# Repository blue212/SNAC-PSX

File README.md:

# SNAC
PSX Accessory converter for MiSTer, by blue212

Serial Native Accessory Converter

SNAC adapter for PSX. This board and psx use 3v3 logic. This is a standalone board, so it's not to used with the SNAC level shifter board. You can use a short male to female usb3.0 extension cable between it and misters USER port.

It has two ports for controllers and a composite port for guncon, also has a header for test points. If a guncon is connected and a justifier isn't the needed signal for Guncon will be output through the composite port.

This version has a solder jumper to connect 5v to the 7.6v pin for rumble. You could not solder the jumper and add external power, but be advised that bad things will happen if you mix up polarity.

-TODO 

-Updates

Added Memory Card add-on board. It uses a 0.8mm thick pcb.

Added files for 3D print cases. Designed by [DiniertoDesigns](https://www.thingiverse.com/thing:5530398)

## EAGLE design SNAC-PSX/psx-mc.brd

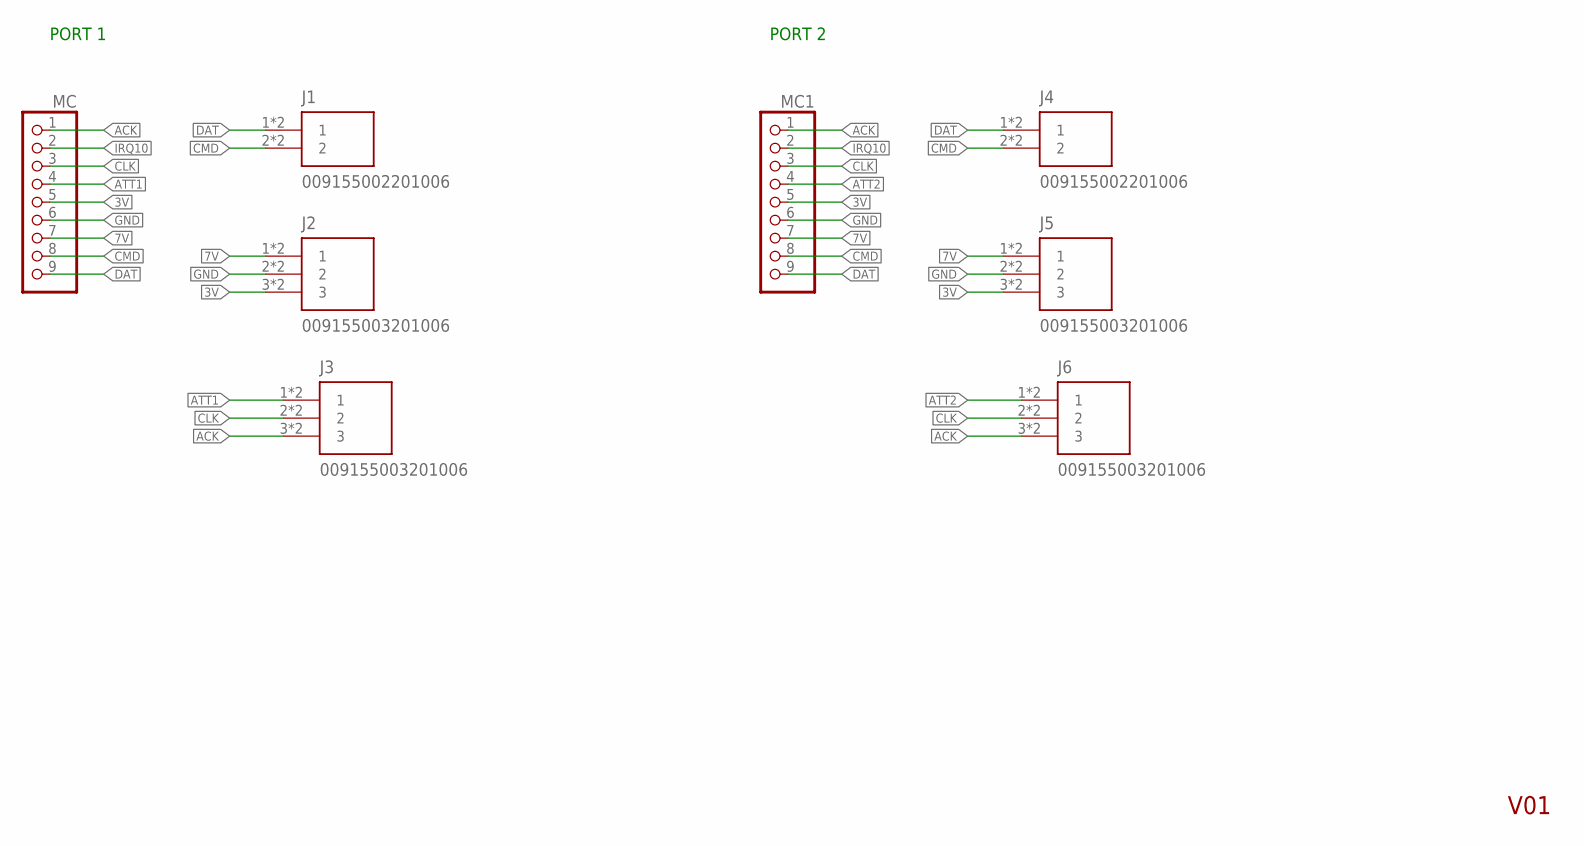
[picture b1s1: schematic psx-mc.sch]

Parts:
J1, J4: 009155002201006; AVX_009155002201006
J2, J3, J5, J6: 009155003201006; AVX_009155003201006
MC, MC1: PINHD-1X09_2.54-S; 1X09-S

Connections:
3V: J2.3, J2.3_1 (3), J5.3, J5.3_1 (3), MC.5, MC1.5
7V: J2.1, J2.1_1 (1), J5.1, J5.1_1 (1), MC.7, MC1.7
ACK: J3.3, J3.3_1 (3), J6.3, J6.3_1 (3), MC.1, MC1.1
ATT1: J3.1, J3.1_1 (1), MC.4
ATT2: J6.1, J6.1_1 (1), MC1.4
CLK: J3.2, J3.2_1 (2), J6.2, J6.2_1 (2), MC.3, MC1.3
CMD: J1.2, J1.2_1 (2), J4.2, J4.2_1 (2), MC.8, MC1.8
DAT: J1.1, J1.1_1 (1), J4.1, J4.1_1 (1), MC.9, MC1.9
GND: J2.2, J2.2_1 (2), J5.2, J5.2_1 (2), MC.6, MC1.6
IRQ10: MC.2, MC1.2

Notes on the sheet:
V01
PORT 1
PORT 2

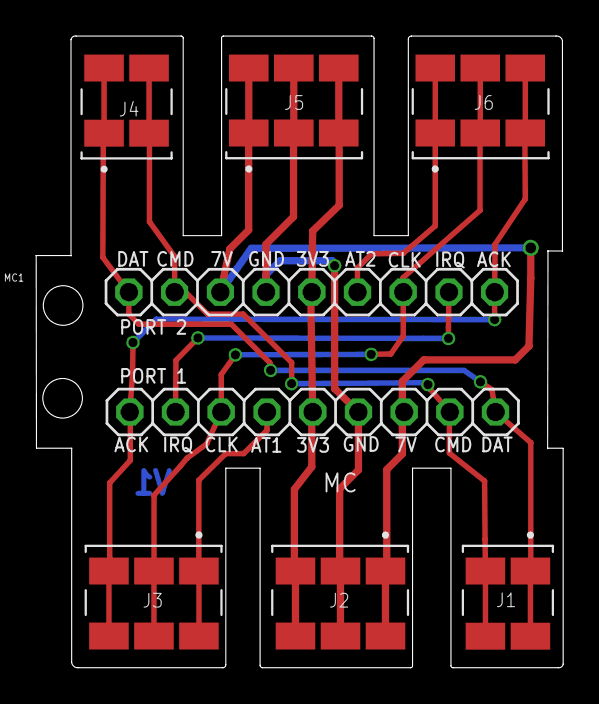
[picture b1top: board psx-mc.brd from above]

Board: 2 copper layers, 29.3 x 35.1 mm, 8 parts (0 on the bottom side), 10 nets.

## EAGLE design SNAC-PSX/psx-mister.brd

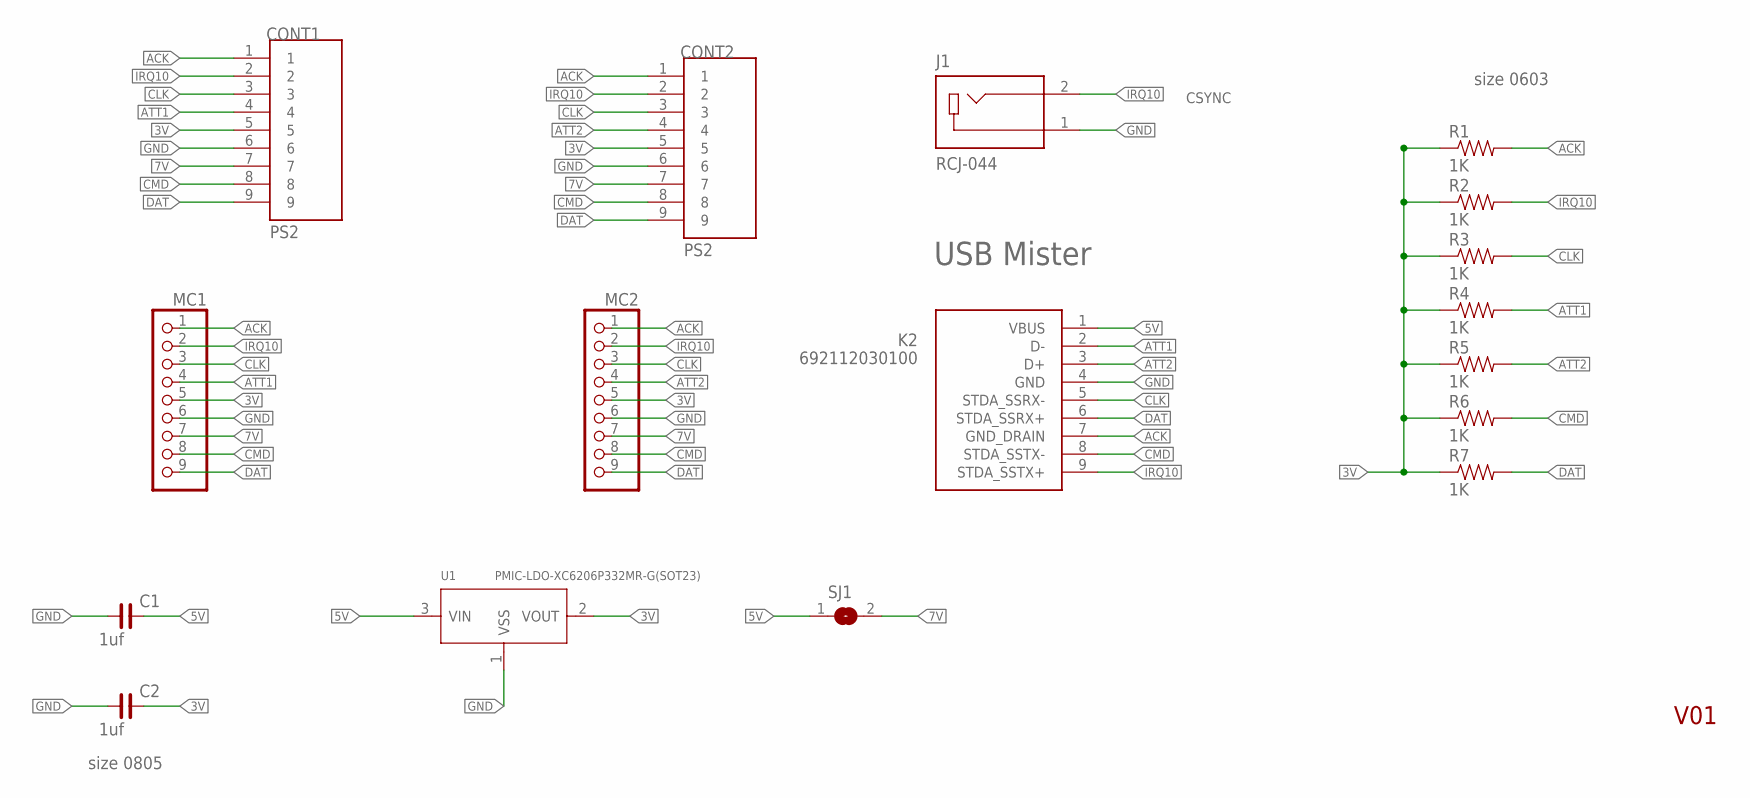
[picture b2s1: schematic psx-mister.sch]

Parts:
C1, C2: 1uf; C0805
CONT1, CONT2: PS2; TE_PS2
J1: RCJ-044; CUI_RCJ-044
K2: 692112030100
MC1, MC2: PINHD-1X09_2.54-S; 1X09-S
R1, R2, R3, R4, R5, R6, R7: 1K; 0603-RES
SJ1: SJ
U1: PMIC-LDO-XC6206P332MR-G(SOT23); SOT-23

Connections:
3V: C2.2, CONT1.5, CONT2.5, MC1.5, MC2.5, R1.1, R2.1, R3.1, R4.1, R5.1, R6.1, R7.1, U1.2 (VOUT)
5V: C1.2, K2.1 (VBUS), SJ1.1, U1.3 (VIN)
7V: CONT1.7, CONT2.7, MC1.7, MC2.7, SJ1.2
ACK: CONT1.1, CONT2.1, K2.7 (GND_DRAIN), MC1.1, MC2.1, R1.2
ATT1: CONT1.4, K2.2 (D-), MC1.4, R4.2
ATT2: CONT2.4, K2.3 (D+), MC2.4, R5.2
CLK: CONT1.3, CONT2.3, K2.5 (STDA_SSRX-), MC1.3, MC2.3, R3.2
CMD: CONT1.8, CONT2.8, K2.8 (STDA_SSTX-), MC1.8, MC2.8, R6.2
DAT: CONT1.9, CONT2.9, K2.6 (STDA_SSRX+), MC1.9, MC2.9, R7.2
GND: C1.1, C2.1, CONT1.6, CONT2.6, J1.1, K2.4 (GND), MC1.6, MC2.6, U1.1 (VSS)
IRQ10: CONT1.2, CONT2.2, J1.2, K2.9 (STDA_SSTX+), MC1.2, MC2.2, R2.2

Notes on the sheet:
V01
USB Mister
size 0805
CSYNC
size 0603

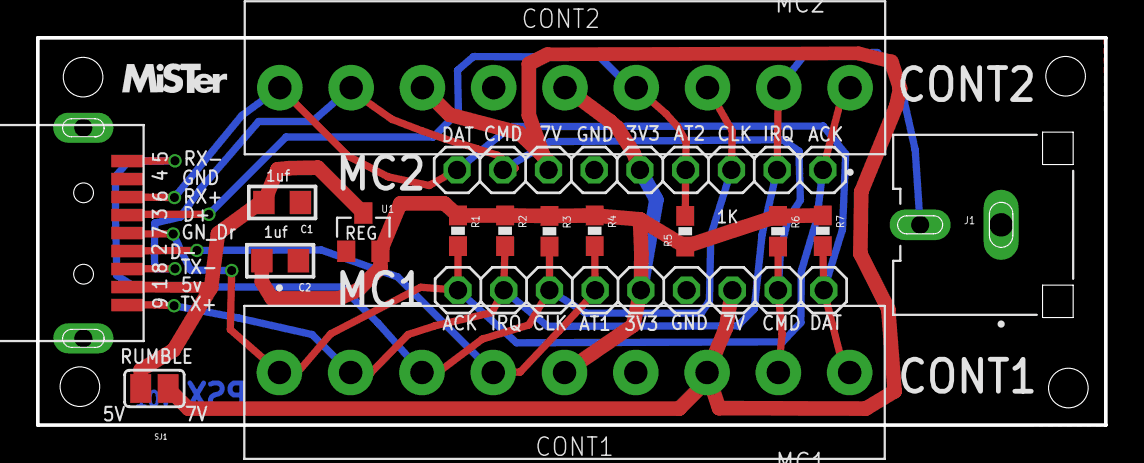
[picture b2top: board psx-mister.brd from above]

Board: 2 copper layers, 59.3 x 21.5 mm, 17 parts (0 on the bottom side), 11 nets.

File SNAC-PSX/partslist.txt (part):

Part  Value                          Device                         Package      Description                                                             AVAILABILITY COMMENT CUI_PURCHASE_URL                                                                                                                                           DESCRIPTION                                                MF              MP      PACKAGE PRICE  PURCHASE-URL                                            
C1    1uf                            C_0805                         C0805        NON-POLARIZED CAP                                                                                                                                                                                                                                                                                                                                                                                                 
C2    1uf                            C_0805                         C0805        NON-POLARIZED CAP                                                                                                                                                                                                                                                                                                                                                                                                 
CONT1 PS2                            PS2                            TE_PS2       Check prices                                                            In Stock     PS2                                                                                                                                                                 Connector Header Through Hole 9 position 0.156 (3.96mm)   TE Connectivity PS2     None    None   https://pricing.snapeda.com/search/part/PS2/?ref=eda    
CONT2 PS2                            PS2                            TE_PS2       Check prices                                                            In Stock     PS2                                                                                                                                                                 Connector Header Through Hole 9 position 0.156 (3.96mm)   TE Connectivity PS2     None    None   https://pricing.snapeda.com/search/part/PS2/?ref=eda    
J1    RCJ-044                        RCJ-044                        CUI_RCJ-044  Metal Right-Angle, RCA Jack, Yellow Housing and Insulation Check prices In Stock             https://www.cuidevices.com/product/interconnect/connectors/r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 Metal Right-Angle, RCA Jack, Yellow Housing and Insulation CUI Devices     RCJ-044 None    None   https://pricing.snapeda.com/search/part/RCJ-044/?ref=eda
K2    692112030100                   692112030100                   692112030100 WR-COM  USB 3.0 SMT PLUG WITH CLIPTYPE A                                                                                                                                                                                                                                                                                                                                                                          
MC1                                  PINHD-1X09_2.54-S              1X09-S       PIN HEADER                                                                                                                                                                                                                                                                                                                                                                                                        
MC2                                  PINHD-1X09_2.54-S              1X09-S       PIN HEADER                                                                                                                                                                                                                                                                                                                                                                                                        
R1    1K                             RESISTOR0603-RES               0603-RES     Resistor                                                                                                                                                                                                                                                                                                                                                                                                          
R2    1K                             RESISTOR0603-RES               0603-RES     Resistor                                                                                                                                                                                                                                                                                                                                                                                                          
R3    1K                             RESISTOR0603-RES               0603-RES     Resistor                                                                                                                                                                                                                                                                                                                                                                                                          
R4    1K                             RESISTOR0603-RES               0603-RES     Resistor                                                                                                                                                                                                                                                                                                                                                                                                          
R5    1K                             RESISTOR0603-RES               0603-RES     Resistor                                                                                                                                                                                                                                                                                                                                                                                                          
R6    1K                             RESISTOR0603-RES               0603-RES     Resistor                                                                                                                                                                                                                                                                                                                                                                                                          
R7    1K                             RESISTOR0603-RES               0603-RES     Resistor                                                                                                                                                                                                                                                                                                                                                                                                          
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
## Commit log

2022-05-01 PSX SNAC
    first test version
2022-08-16 Add Memory Card PCB
    optional add on board
2022-11-19 Added cases
2024-02-07 added case

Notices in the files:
parts and their libraries:
Wuerth_Elektronik_eiCan_Communication_Co: Copyright: Würth Elektronik
rc-master-smd: Copyright (C) 2007, Bob Starr
SparkFun: Licensing: CC v3.0 Share-Alike You are welcome to use this library for commercial purposes.
